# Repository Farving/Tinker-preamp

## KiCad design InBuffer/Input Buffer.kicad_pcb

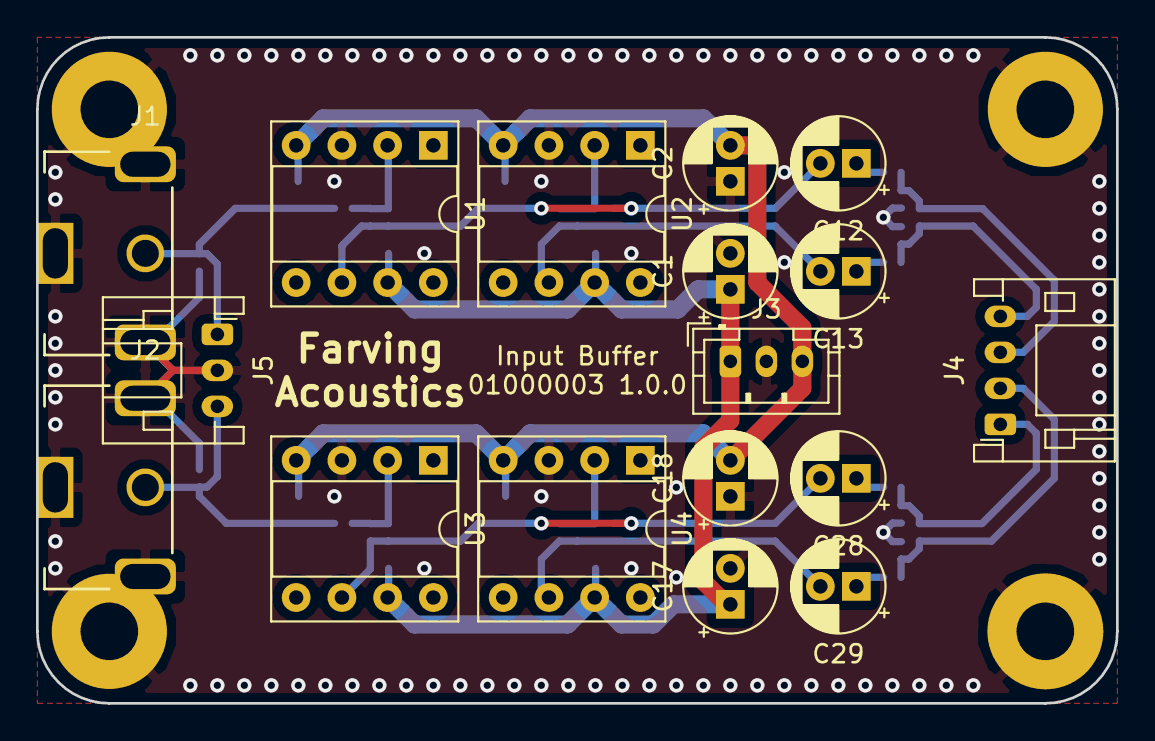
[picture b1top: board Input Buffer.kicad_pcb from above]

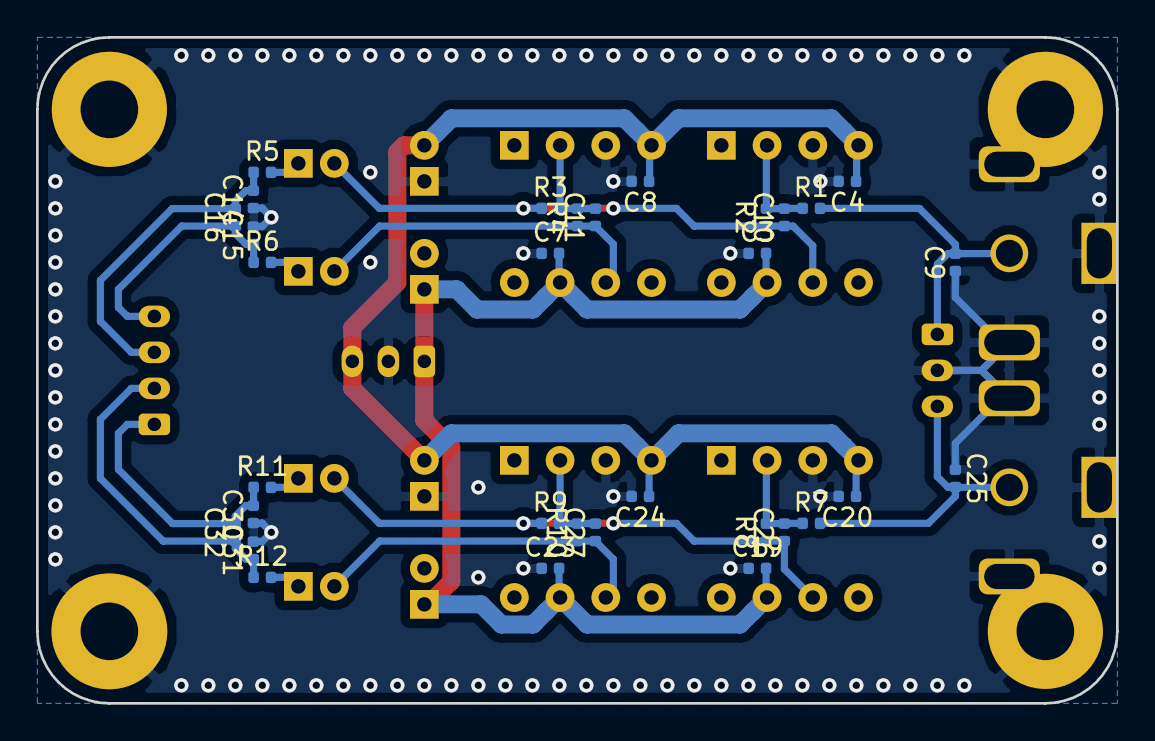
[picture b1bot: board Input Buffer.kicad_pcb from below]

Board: 2 copper layers, 60.0 x 37.0 mm, 50 parts (32 on the bottom side), 21 nets.

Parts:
C1, C2, C12, C13, C17, C18, C28, C29: 10u; CP_Radial_D5.0mm_P2.00mm
C3, C4, C7, C8, C16, C19, C20, C23, C24, C32: 100n; C_0402_1005Metric
C9, C25: 100p; C_0402_1005Metric
C10, C11, C26, C27: 120p; C_0402_1005Metric
C14, C15, C30, C31: 1n; C_0402_1005Metric
J1: RND 205-00698; RCA_Horizontal_RNDConnect
J2: RND 205-00699; RCA_Horizontal_RNDConnect
J3: JST_PH_B3B-PH-K; JST_PH_B3B-PH-K_1x03_P2.00mm_Vertical
J4: JST_PH_S4B-PH-K; JST_PH_S4B-PH-K_1x04_P2.00mm_Horizontal
J5: JST_PH_S3B-PH-K; JST_PH_S3B-PH-K_1x03_P2.00mm_Horizontal
PCB1: Board_Module; PCB_Board_60x37
R1, R2, R3, R4, R7, R8, R9, R10: 5k76; R_0402_1005Metric
R5, R6, R11, R12: 237R; R_0402_1005Metric
U1, U2, U3, U4: AD797; DIP-8_W7.62mm_Socket

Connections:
+15V: C1.1, C3.2, C7.2, C17.1, C19.2, C23.2, J3.1, U1.7, U2.7, U3.7, U4.7
-15V: C2.2, C4.1, C8.1, C18.2, C20.1, C24.1, J3.3, U1.4, U2.4, U3.4, U4.4
/Phono_L_Buffer/In: C9.2, J1.T, J5.1, R1.2
/Phono_L_Buffer/OutN: C14.2, C16.2, J4.3, R5.1
/Phono_L_Buffer/OutP: C15.1, C16.1, J4.4, R6.1
/Phono_R_Buffer/In: C25.2, J2.T, J5.3, R7.2
/Phono_R_Buffer/OutN: C30.2, C32.2, J4.1, R11.1
/Phono_R_Buffer/OutP: C31.1, C32.1, J4.2, R12.1
GNDA: C1.2, C2.1, C3.1, C4.2, C7.1, C8.2, C9.1, C14.1, C15.2, C17.2, C18.1, C19.1, C20.2, C23.1, C24.2, C25.1, C30.1, C31.2, J1.S, J2.S, J3.2, J5.2, PCB1.1, PCB1.2, PCB1.3, PCB1.4, U1.3, U2.3, U3.3, U4.3
unnamed: C10.1, C12.2, R2.1, R3.1, U1.6
unnamed: C10.2, R1.1, R2.2, U1.2
unnamed: C11.1, C13.2, R4.1, U2.6
unnamed: C11.2, R3.2, R4.2, U2.2
unnamed: C12.1, R5.2
unnamed: C13.1, R6.2
unnamed: C26.1, C28.2, R8.1, R9.1, U3.6
unnamed: C26.2, R7.1, R8.2, U3.2
unnamed: C27.1, C29.2, R10.1, U4.6
unnamed: C27.2, R9.2, R10.2, U4.2
unnamed: C28.1, R11.2
unnamed: C29.1, R12.2

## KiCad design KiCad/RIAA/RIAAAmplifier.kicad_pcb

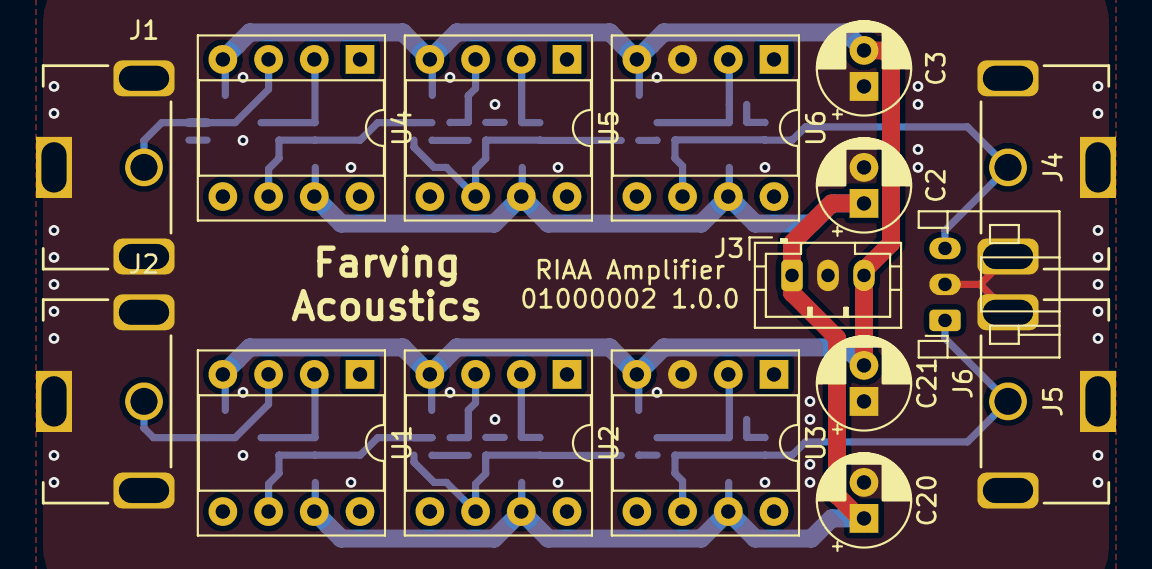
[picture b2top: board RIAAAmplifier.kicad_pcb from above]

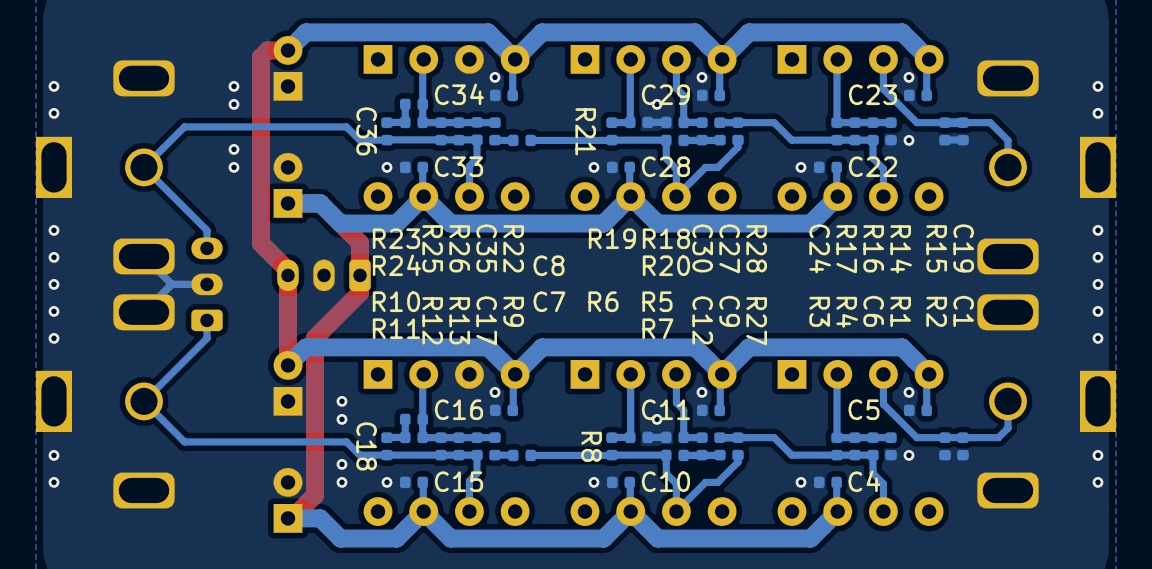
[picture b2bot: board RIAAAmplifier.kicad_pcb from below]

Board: 2 copper layers, 70 parts (54 on the bottom side), 25 nets.

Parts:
C1, C19: 100p; C_0402_1005Metric
C2, C3, C20, C21: 10u; CP_Radial_D5.0mm_P2.00mm
C4, C5, C10, C11, C15, C16, C22, C23, C28, C29, C33, C34: 100n; C_0402_1005Metric
C6, C9, C12, C24, C27, C30: 33n; C_0402_1005Metric
C7, C8: 3.3n; C_0402_1005Metric
C17, C35: 750p; C_0402_1005Metric
C18, C36: 68n; C_0402_1005Metric
J1, J4: RND 205-00698; RCA_Horizontal_RNDConnect
J2, J5: RND 205-00699; RCA_Horizontal_RNDConnect
J3: JST_PH_B3B-PH-K; JST_PH_B3B-PH-K_1x03_P2.00mm_Vertical
J6: JST_PH_S3B-PH-K; JST_PH_S3B-PH-K_1x03_P2.00mm_Horizontal
R1, R14: 100k; R_0402_1005Metric
R2, R13, R15, R26: 47k; R_0402_1005Metric
R3, R16: 43k; R_0402_1005Metric
R4, R17: 2.4k; R_0402_1005Metric
R5, R7, R18, R20: 270k; R_0402_1005Metric
R6, R8, R11, R19, R21, R24: 4.7k; R_0402_1005Metric
R9, R22: 560R; R_0402_1005Metric
R10, R23: 1M; R_0402_1005Metric
R12, R25: 402k; R_0402_1005Metric
R27, R28: NM; R_0402_1005Metric
U1, U4: LT1115; DIP-8_W7.62mm_Socket
U2, U3, U5, U6: AD797; DIP-8_W7.62mm_Socket

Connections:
+15V: C2.1, C4.2, C10.2, C15.2, C20.1, C22.2, C28.2, C33.2, J3.1, U1.7, U2.7, U3.7, U4.7, U5.7, U6.7
-15V: C3.2, C5.1, C11.1, C16.1, C21.2, C23.1, C29.1, C34.1, J3.3, U1.4, U2.4, U3.4, U4.4, U5.4, U6.4
/RIAA_L/In: C19.2, J1.T, R15.1, U4.3
/RIAA_L/Out: C35.1, C36.1, J4.T, J6.3, R25.1, R26.1, U6.6
/RIAA_R/In: C1.2, J2.T, R2.1, U1.3
/RIAA_R/Out: C17.1, C18.1, J5.T, J6.1, R12.1, R13.1, U3.6
GNDA: C1.1, C2.2, C3.1, C4.1, C5.2, C10.1, C11.2, C15.1, C16.2, C19.1, C20.2, C21.1, C22.1, C23.2, C28.1, C29.2, C33.1, C34.2, J1.S, J2.S, J3.2, J4.S, J5.S, J6.2, R1.2, R2.2, R5.2, R6.2, R14.2, R15.2, R18.2, R19.2, U3.3, U6.3
unnamed: C6.1, C9.2, R3.1, R4.1, R27.2, U1.6
unnamed: C6.2, R1.1, R3.2, R4.2, U1.2
unnamed: C7.1, R9.2
unnamed: C7.2, R7.1, R8.1, R27.1, U2.6
unnamed: C8.1, R22.2
unnamed: C8.2, R20.1, R21.1, R28.1, U5.6
unnamed: C12.1, R5.1, U2.3
unnamed: C9.1, C12.2, R7.2
unnamed: C17.2, R9.1, R10.2, R11.2, R12.2, R13.2, U3.2
unnamed: C18.2, R10.1, R11.1
unnamed: C24.1, C27.2, R16.1, R17.1, R28.2, U4.6
unnamed: C24.2, R14.1, R16.2, R17.2, U4.2
unnamed: C27.1, C30.2, R20.2
unnamed: C30.1, R18.1, U5.3
unnamed: C35.2, R22.1, R23.2, R24.2, R25.2, R26.2, U6.2
unnamed: C36.2, R23.1, R24.1
unnamed: R6.1, R8.2, U2.2
unnamed: R19.1, R21.2, U5.2

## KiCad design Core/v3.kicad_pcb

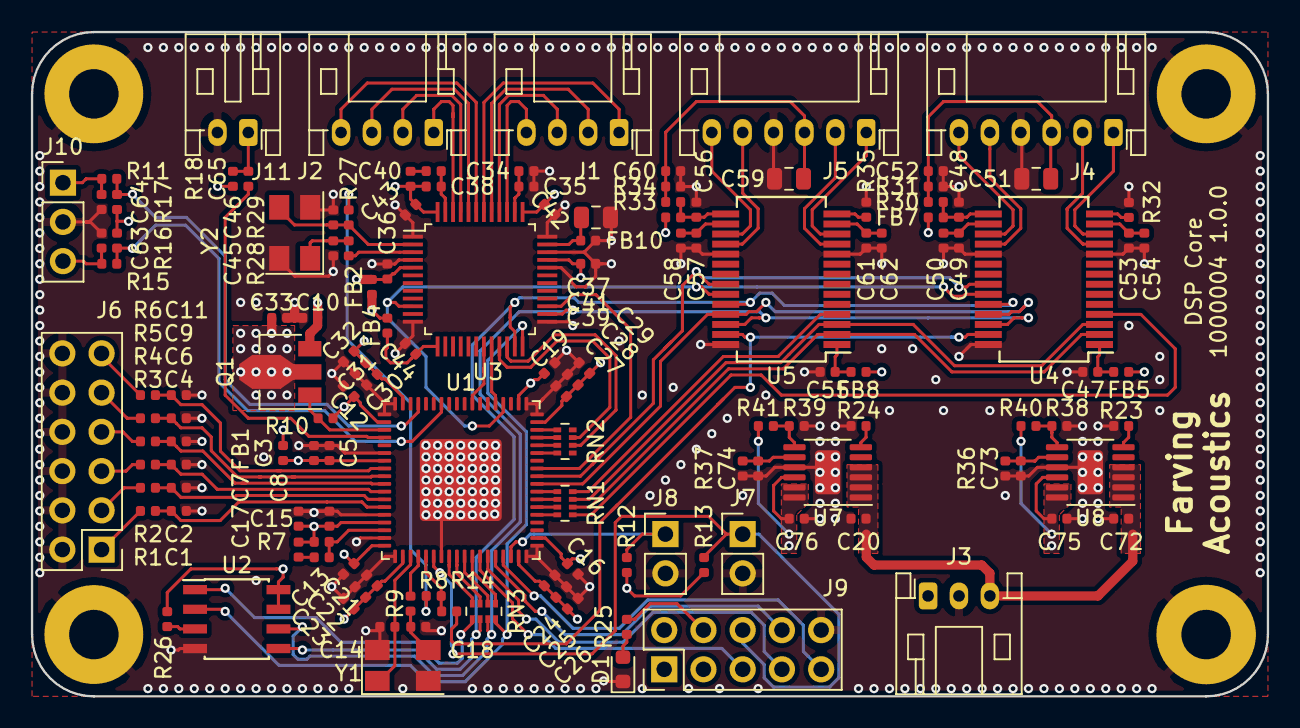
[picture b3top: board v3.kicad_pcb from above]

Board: 4 copper layers, 80.0 x 43.0 mm, 140 parts (0 on the bottom side), 114 nets.

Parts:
C1, C2, C4, C5, C6, C8, C9, C11, C12, C13, C16, C19, C22, C25, C28, C31, C35, C36, C39, C41, C42, C43, C44, C47, C48, C49, C52, C53, C55, C56, C57, C60, C61: 100n; C_0402_1005Metric
C3, C7, C10, C20, C33, C34, C50, C54, C58, C62, C72, C75, C76: 10u; C_0402_1005Metric
C14, C18, C45, C46: 22p; C_0402_1005Metric
C15: 150p; C_0402_1005Metric
C17: 5.6n; C_0402_1005Metric
C21, C24, C27, C30, C63, C64, C65: 10n; C_0402_1005Metric
C23, C26, C29, C32, C73, C74: 1u; C_0402_1005Metric
C37, C51, C59: 47u; C_0805_2012Metric
C38: 2.2n; C_0402_1005Metric
C40: 39n; C_0402_1005Metric
D1: LED_Small; LED_0603_1608Metric
FB1: Ferrite_Bead_Small; L_0402_1005Metric
FB2, FB4, FB5, FB7, FB8, FB10: 600Z; L_0402_1005Metric
J1, J2: JST_PH_S4B-PH-K; JST_PH_S4B-PH-K_1x04_P2.00mm_Horizontal
J3: JST_PH_S3B-PH-K; JST_PH_S3B-PH-K_1x03_P2.00mm_Horizontal
J4, J5: JST_PH_S6B-PH-K; JST_PH_S6B-PH-K_1x06_P2.00mm_Horizontal
J6: Conn_02x06_Odd_Even; PinHeader_2x06_P2.54mm_Vertical
J7, J8: Conn_01x02_Male; PinHeader_1x02_P2.54mm_Vertical
J9: Conn_02x05_Odd_Even; PinHeader_2x05_P2.54mm_Vertical
J10: Conn_01x03_Male; PinHeader_1x03_P2.54mm_Vertical
J11: Conn_01x02_Male; JST_PH_S2B-PH-K_1x02_P2.00mm_Horizontal
PCB1: Board_Module; PCB_Board_70x43
Q1: 2STF2550; SOT-89-3
R1, R2, R3, R4, R5, R6: 120R; R_0402_1005Metric
R7: 4.32k; R_0402_1005Metric
R8, R14: 33R; R_0402_1005Metric
R9, R28: 49.9R; R_0402_1005Metric
R10, R25: 1k; R_0402_1005Metric
R11, R12, R13, R15, R16, R17, R18, R26: 10k; R_0402_1005Metric
R23, R24, R29: 0R; R_0402_1005Metric
R27: 3.32k; R_0402_1005Metric
R30, R33: 2.21k; R_0402_1005Metric
R31, R34: 2.8k; R_0402_1005Metric
R32, R35: 2.49k; R_0402_1005Metric
R36: 5k; R_0402_1005Metric
R37: 3.3k; R_0402_1005Metric
R38, R39: 18k; R_0402_1005Metric
R40, R41: 750k; R_0402_1005Metric
RN1, RN2: R_Pack04; R_Array_Concave_4x0402
RN3: 120R; R_Array_Concave_4x0402
U1: ADAU1452; LFCSP-72-1EP_10x10mm_P0.5mm_EP5.3x5.3mm
U2: 24AA1024; SOIC-8_3.9x4.9mm_P1.27mm
U3: AD1974; LQFP-48_7x7mm_P0.5mm
U4, U5: AD1955; SSOP-28_5.3x10.2mm_P0.65mm
U7, U8: LT3045; MSOP-12-1EP_3x4mm_P0.65mm_EP1.65x2.85mm
Y1, Y2: 12.288MHz; Crystal_SMD_5032-4Pin_5.0x3.2mm

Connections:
+3V3: C76.1, FB2.1, FB4.1, R41.1, U7.10, U7.11, U7.12
+5V: C75.1, FB5.1, FB7.1, FB8.1, FB10.1, R40.1, U8.10, U8.11, U8.12
/6V: C20.1, C72.1, J3.3, U7.1, U7.2, U7.3, U7.4, U8.1, U8.2, U8.3, U8.4
/ADC/I2S_BCLK: RN2.7, U3.21
/ADC/I2S_LRCLK: RN2.6, U3.22
/ADC/I2S_SDIN1: U1.59, U3.20
/ADC/I2S_SDIN2: U1.62, U3.19
/ADC/In_L0N: J1.3, U3.40
/ADC/In_L0P: J1.4, U3.39
/ADC/In_L1N: J2.3, U3.44
/ADC/In_L1P: J2.4, U3.43
/ADC/In_R0N: J1.1, U3.42
/ADC/In_R0P: J1.2, U3.41
/ADC/In_R1N: J2.1, U3.46
/ADC/In_R1P: J2.2, U3.45
/ADC/SPI_CLK: RN3.7, U2.6, U3.26, U4.26, U5.26
/ADC/SPI_CS: U1.47, U3.27
/ADC/SPI_MISO: RN3.8, U2.2, U3.24
/ADC/SPI_MOSI: RN3.6, U2.5, U3.23, U4.24, U5.24
/DAC1/I2S_BCLK: RN1.7, U4.3, U5.3
/DAC1/I2S_LRCLK: RN1.6, U4.2, U5.2
/DAC1/I2S_MCLK: R14.1, U4.27, U5.27
/DAC1/I2S_SDOUT: RN1.5, U4.4
/DAC1/Out_LN: J4.6, U4.17
/DAC1/Out_LP: J4.5, U4.18
/DAC1/Out_RN: J4.1, U4.12
/DAC1/Out_RP: J4.2, U4.11
/DAC1/SPI_CS: U1.45, U4.25, U5.25
/DAC1/Vbias: C51.1, C52.1, J4.3, R30.1, R31.1
/DAC2/I2S_SDOUT: RN1.8, U5.4
/DAC2/Out_LN: J5.6, U5.17
/DAC2/Out_LP: J5.5, U5.18
/DAC2/Out_RN: J5.1, U5.12
/DAC2/Out_RP: J5.2, U5.11
/DAC2/Vbias: C59.1, C60.1, J5.3, R33.1, R34.1
/DSP/A-MP12: R15.1, R16.2, U1.66
/DSP/B-MP13: R11.1, R17.2, U1.69
/DSP/DVDD: C21.1, C22.1, C23.1, C24.1, C25.1, C26.1, C27.1, C28.1, C29.1, C30.1, C31.1, C32.1, C33.1, Q1.2, U1.20, U1.35, U1.53, U1.71
/DSP/ENABLE: U1.58, U3.10, U4.23, U5.23
/DSP/I2S_MCLK_ADC: R8.2, R29.2
/DSP/MCLK: R8.1, R14.2, U1.23
/DSP/MISO: J9.5, U1.30
/DSP/MOSI: J9.8, U1.32
/DSP/MUTE: U1.46, U4.22, U5.22
/DSP/SCLK: J9.7, U1.31
/DSP/SPDIF_IN: C65.2, U1.4
/DSP/SS: J9.9, U1.33
/DSP/nRESET: J7.1, J9.6, R13.1, U1.24
GND: C1.2, C2.2, C3.2, C4.2, C5.2, C6.2, C7.2, C8.2, C9.2, C10.2, C11.2, C12.2, C13.2, C14.2, C16.2, C18.2, C19.2, C20.2, C21.2, C22.2, C23.2, C24.2, C25.2, C26.2, C27.2, C28.2, C29.2, C30.2, C31.2, C32.2, C33.2, C34.2, C35.2, C36.2, C37.2, C39.2, C41.2, C42.2, C43.2, C44.2, C45.2, C46.2, C47.2, C48.2, C49.2, C50.2, C51.2, C52.2, C53.2, C54.2, C55.2, C56.2, C57.2, C58.2, C59.2, C60.2, C61.2, C62.2, C63.2, C64.2, C72.2, C73.2, C74.2, C75.2, C76.2, D1.1, J3.2, J4.4, J5.4, J6.2, J6.4, J6.6, J6.8, J6.10, J6.12, J7.2, J8.2, J9.10, J10.2, J11.2, PCB1.1, PCB1.2, PCB1.3, PCB1.4, R23.2, R24.2, R31.2, R32.2, R34.2, R35.2, R36.2, R37.2, R38.2, R39.2, U1.1, U1.6, U1.14, U1.17, U1.19, U1.25, U1.36, U1.37, U1.54, U1.55, U1.72, U1.73, U2.4, U3.1, U3.4, U3.12, U3.25, U3.32, U3.34, U3.36, U4.10, U4.19, U4.28, U5.10, U5.19, U5.28, U7.9, U7.13, U8.9, U8.13, Y1.2, Y1.4, Y2.2, Y2.4
unnamed: C1.1, R1.1, U1.13
unnamed: C2.1, R2.1, U1.12
unnamed: C4.1, R3.1, U1.11
unnamed: C6.1, R4.1, U1.10
unnamed: C9.1, R5.1, U1.9
unnamed: C11.1, R6.1, U1.8
unnamed: C14.1, U1.21, Y1.1
unnamed: C15.2, R7.2, U1.16
unnamed: C17.2, R7.1
unnamed: C18.1, R9.2, Y1.3
unnamed: C34.1, C35.1, U3.38
unnamed: C36.1, C38.1, C39.1, C42.1, C43.1, FB2.2, R27.1, U3.5, U3.33, U3.37, U3.48
unnamed: C37.1, C41.1, U3.35
unnamed: C38.2, C40.2, U3.47
unnamed: C40.1, R27.2
unnamed: C44.1, FB4.2, U3.13
unnamed: C45.1, R28.2, Y2.1
unnamed: C46.1, R29.1, U3.2, Y2.3
unnamed: C47.1, FB5.2, U4.1
unnamed: C48.1, FB7.2, R30.2, U4.15
unnamed: C49.1, C50.1, U4.16
unnamed: C53.1, C54.1, U4.13
unnamed: C55.1, FB8.2, U5.1
unnamed: C56.1, FB10.2, R33.2, U5.15
unnamed: C57.1, C58.1, U5.16
unnamed: C61.1, C62.1, U5.13
unnamed: C63.1, J10.3, R15.2
unnamed: C64.1, J10.1, R11.2
unnamed: C65.1, J11.1, R18.2
unnamed: C73.1, R36.1, U8.8
unnamed: C74.1, R37.1, U7.8
unnamed: D1.2, R25.2
unnamed: J6.1, R1.2
unnamed: J6.3, R2.2
unnamed: J6.5, R3.2
unnamed: J6.7, R4.2
unnamed: J6.9, R5.2
unnamed: J6.11, R6.2
unnamed: J8.1, R12.1, U1.34
unnamed: J9.4, R25.1
unnamed: Q1.1, R10.1, U1.3
unnamed: R9.1, U1.22
unnamed: R23.1, U8.6
unnamed: R24.1, U7.6
unnamed: R26.2, U2.3
unnamed: R28.1, U3.3
unnamed: R32.1, U4.14
unnamed: R35.1, U5.14
unnamed: R38.1, R40.2, U8.7
unnamed: R39.1, R41.2, U7.7
unnamed: RN1.1, U1.44
unnamed: RN1.2, U1.43
unnamed: RN1.3, U1.42
unnamed: RN1.4, U1.41
unnamed: RN2.1, U1.52
unnamed: RN2.2, U1.51
unnamed: RN2.3, U1.50
unnamed: RN2.4, U1.49
unnamed: RN3.1, U1.29
unnamed: RN3.2, U1.28
unnamed: RN3.3, U1.27
unnamed: RN3.4, U1.26
unnamed: RN3.5, U2.1
VDD: C10.1, C12.1, C13.1, C16.1, C19.1, FB1.1, J3.1, Q1.3, R10.2, R12.2, R13.2, R16.1, R17.1, R18.1, R26.1, U1.2, U1.18, U1.38, U1.56, U2.7, U2.8
VDDA: C3.1, C5.1, C7.1, C8.1, C15.1, C17.1, FB1.2, U1.7, U1.15

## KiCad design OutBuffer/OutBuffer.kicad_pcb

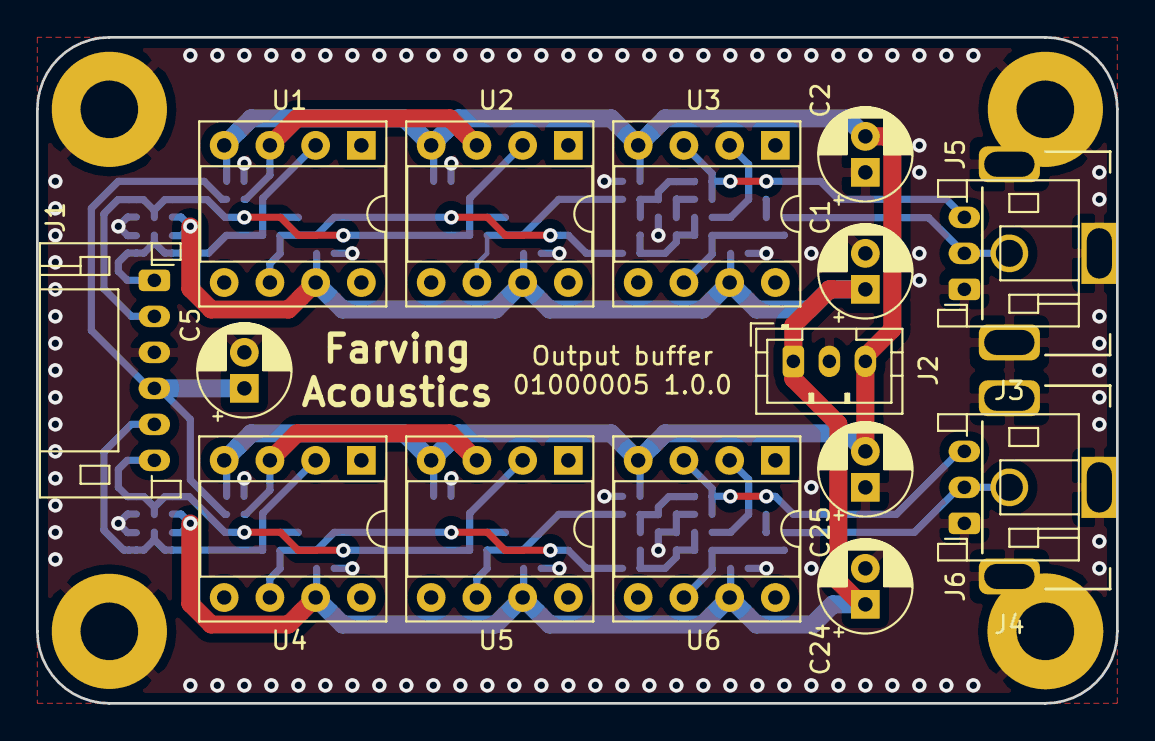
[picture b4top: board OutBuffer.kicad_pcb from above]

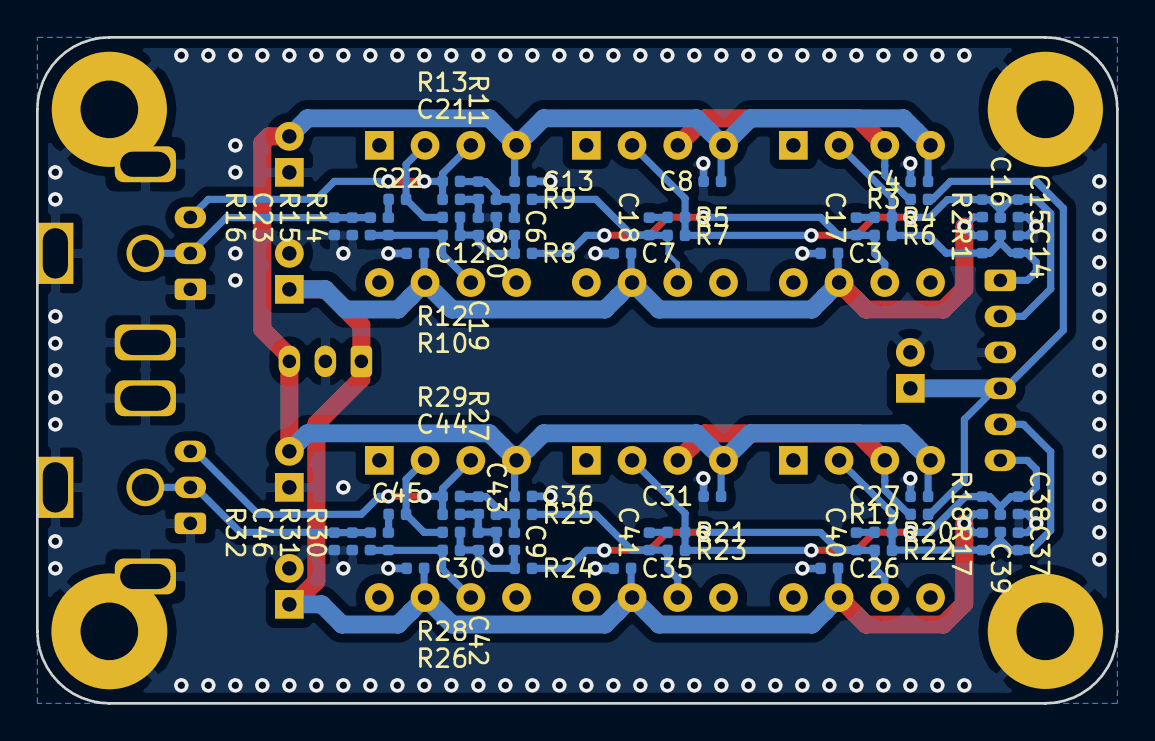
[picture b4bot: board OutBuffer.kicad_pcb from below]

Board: 2 copper layers, 60.0 x 37.0 mm, 84 parts (66 on the bottom side), 32 nets.

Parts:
C1, C2, C5, C24, C25: 10u; CP_Radial_D5.0mm_P2.00mm
C3, C4, C7, C8, C12, C13, C16, C26, C27, C30, C31, C35, C36, C39: 100n; C_0402_1005Metric
C6, C9: 390p; C_0402_1005Metric
C14, C15, C37, C38: 1n; C_0402_1005Metric
C17, C18, C40, C41: 100p; C_0402_1005Metric
C19, C20, C42, C43: 5n6; C_0402_1005Metric
C21, C22, C44, C45: 2n7; C_0402_1005Metric
C23, C46: 3n9; C_0402_1005Metric
J1: JST_PH_S6B-PH-K; JST_PH_S6B-PH-K_1x06_P2.00mm_Horizontal
J2: JST_PH_B3B-PH-K; JST_PH_B3B-PH-K_1x03_P2.00mm_Vertical
J3, J4: RND 205-00698; RCA_Horizontal_RNDConnect
J5, J6: JST_PH_S3B-PH-K; JST_PH_S3B-PH-K_1x03_P2.00mm_Horizontal
PCB1: Board_Module; PCB_Board_60x37
R1, R2, R6, R7, R17, R18, R22, R23: 2k; R_0402_1005Metric
R3, R19: 5k76; R_0402_1005Metric
R4, R5, R14, R20, R21, R30: 100R; R_0402_1005Metric
R8, R9, R24, R25: 681R; R_0402_1005Metric
R10, R11, R26, R27: 226R; R_0402_1005Metric
R12, R13, R28, R29: 324R; R_0402_1005Metric
R15, R31: 332R; R_0402_1005Metric
R16, R32: NM; R_0402_1005Metric
U1, U2, U3, U4, U5, U6: AD797; DIP-8_W7.62mm_Socket

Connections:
+15V: C1.1, C3.2, C7.2, C12.2, C24.1, C26.2, C30.2, C35.2, J2.1, R1.2, R2.1, R17.2, R18.1, U1.7, U2.7, U3.7, U4.7, U5.7, U6.7
-15V: C2.2, C4.1, C8.1, C13.1, C25.2, C27.1, C31.1, C36.1, J2.3, U1.4, U2.4, U3.4, U4.4, U5.4, U6.4
/Output_L_Buffer/InN: C15.1, C16.1, J1.2, R2.2, R5.2, R7.2, U2.2
/Output_L_Buffer/InP: C14.2, C16.2, J1.1, R1.1, R4.2, R6.2, U1.2
/Output_L_Buffer/OutN: C23.2, J3.T, J5.2, R15.1, R16.1
/Output_L_Buffer/OutP: C21.2, J5.3, R13.1, U3.3
/Output_L_Buffer/Vbias: C5.1, J1.4, R3.2, R19.2
/Output_R_Buffer/InN: C38.1, C39.1, J1.6, R18.2, R21.2, R23.2, U5.2
/Output_R_Buffer/InP: C37.2, C39.2, J1.5, R17.1, R20.2, R22.2, U4.2
/Output_R_Buffer/OutN: C46.2, J4.T, J6.2, R31.1, R32.1
/Output_R_Buffer/OutP: C44.2, J6.3, R29.1, U6.3
GNDA: C1.2, C2.1, C3.1, C4.2, C5.2, C7.1, C8.2, C12.1, C13.2, C14.1, C15.2, C19.1, C20.2, C21.1, C23.1, C24.2, C25.1, C26.1, C27.2, C30.1, C31.2, C35.1, C36.2, C37.1, C38.2, C42.1, C43.2, C44.1, C46.1, J1.3, J2.2, J3.S, J4.S, J5.1, J6.1, PCB1.1, PCB1.2, PCB1.3, PCB1.4, R11.2, R16.2, R27.2, R32.2
unnamed: C17.1, R6.1, R8.2, U1.6
unnamed: C17.2, R4.1
unnamed: C18.1, R7.1, R9.2, U2.6
unnamed: C18.2, R5.1
unnamed: C6.2, C19.2, R8.1, R10.2, R12.2
unnamed: C6.1, C20.1, R9.1, R11.1, R13.2
unnamed: C22.1, R14.2
unnamed: C22.2, R12.1, U3.2
unnamed: C40.1, R22.1, R24.2, U4.6
unnamed: C40.2, R20.1
unnamed: C41.1, R23.1, R25.2, U5.6
unnamed: C41.2, R21.1
unnamed: C9.2, C42.2, R24.1, R26.2, R28.2
unnamed: C9.1, C43.1, R25.1, R27.1, R29.2
unnamed: C45.1, R30.2
unnamed: C45.2, R28.1, U6.2
unnamed: R3.1, U1.3, U2.3
unnamed: R10.1, R14.1, R15.2, U3.6
unnamed: R19.1, U4.3, U5.3
unnamed: R26.1, R30.1, R31.2, U6.6

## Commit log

2018-11-13 Updated gitignore
2018-11-13 Update gitignore
2019-05-07 Major Overhaul
    Project split into subprojects
    RIAA 1.0.0 Released
    Buffers ready for release
    Core in progress
2019-05-08 Added project library
2019-05-08 Change footprint for 2p pin headers
2019-05-08 Add partial routing
2019-05-10 Update partial routing
2019-05-16 Add missing symbols from transfer
2019-05-23 Add complete routing
2019-05-29 Update library
2019-05-29 Add RIAA simulations
2019-06-11 Release 1.0.0
2019-06-11 Add simulations of filters
2019-06-11 Add v3 pcb - temporary file
2019-06-11 Remove production files
2019-06-11 Add cache files
2019-06-11 Folder restructure
2019-06-11 Remove leftovers from cleanup
2019-07-29 Update OpAmp to KiCad Library symbol
